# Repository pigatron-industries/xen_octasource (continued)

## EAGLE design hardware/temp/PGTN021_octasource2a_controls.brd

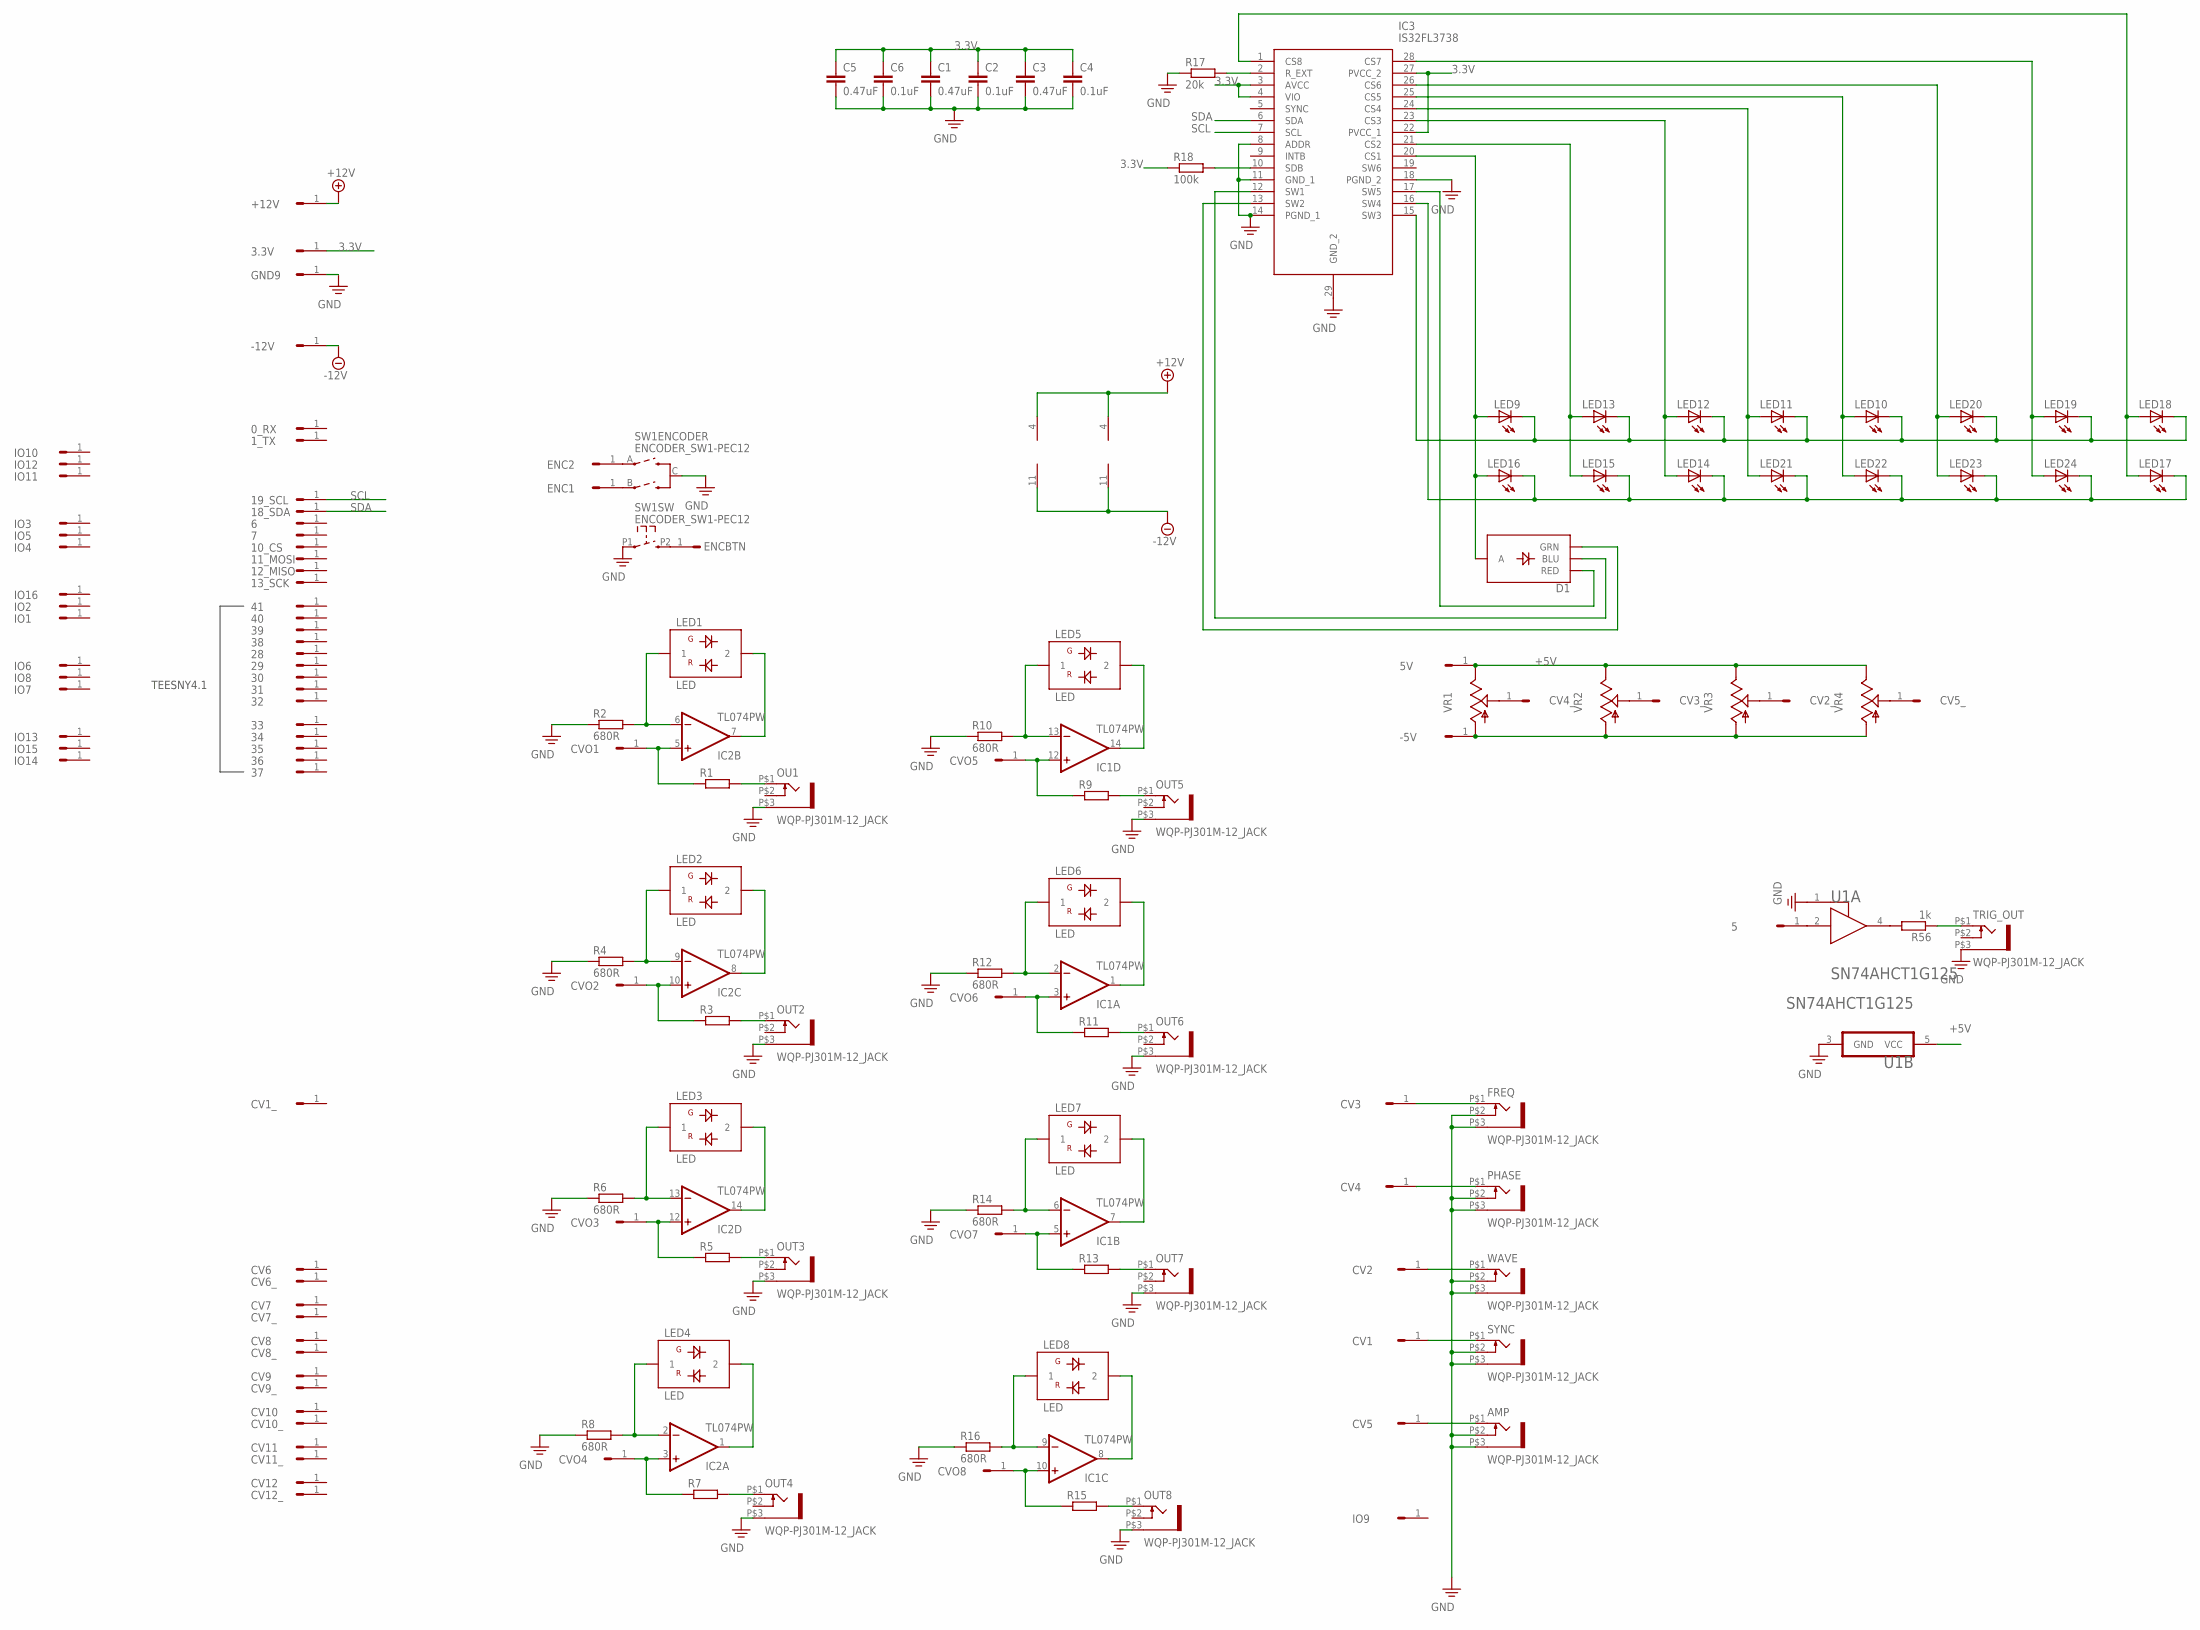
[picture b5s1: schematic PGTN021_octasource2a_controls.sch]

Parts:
0_RX, 1_TX, 3.3V, 5, 5V, 6, 7, 10_CS, 11_MOSI, 12_MISO, 13_SCK, 18_SDA, 19_SCL, 28, 29, 30, 31, 32, 33, 34, 35, 36, 37, 38, 39, 40, 41: HEADER/MALE/01
+12V: HEADER/MALE/01
-5V, -12V: HEADER/MALE/01
AMP: WQP-PJ301M-12_JACK
C1, C3, C5: 0.47uF; C0603
C2, C4, C6: 0.1uF; C0603
CV1, CV1_, CV2, CV2_, CV3, CV3_, CV4, CV4_, CV5, CV5_, CV6, CV6_, CV7, CV7_, CV8, CV8_, CV9, CV9_, CV10, CV10_, CV11, CV11_, CV12, CV12_: HEADER/MALE/01
CVO1, CVO2, CVO3, CVO4, CVO5, CVO6, CVO7, CVO8: HEADER/MALE/01
D1: LED-RGB-CADIALIGHT1210; CHIPLED_1210
ENC1, ENC2: HEADER/MALE/01
ENCBTN: HEADER/MALE/01
FREQ: WQP-PJ301M-12_JACK
GND9: HEADER/MALE/01
IC1, IC2: TL074PW; TSSOP14
IC3: IS32FL3738; TSSOP29
IO1, IO2, IO3, IO4, IO5, IO6, IO7, IO8, IO9, IO10, IO11, IO12, IO13, IO14, IO15, IO16: HEADER/MALE/01
LED1, LED2, LED3, LED4, LED5, LED6, LED7, LED8: LED; OG-LEDS_LED3MM
LED9, LED10, LED11, LED12, LED13, LED14, LED15, LED16, LED17, LED18, LED19, LED20, LED21, LED22, LED23, LED24: LEDCHIPLED_0805; CHIPLED_0805
OU1: WQP-PJ301M-12_JACK
OUT2, OUT3, OUT4, OUT5, OUT6, OUT7, OUT8: WQP-PJ301M-12_JACK
PHASE: WQP-PJ301M-12_JACK
R1, R3, R5, R7, R9, R11, R13, R15: RESISTOR; R0603
R2, R4, R6, R8, R10, R12, R14, R16: 680R; R0603
R17: 20k; R0603
R18: 100k; R0603
R56: 1k; R0603
SW1: ENCODER_SW1-PEC12; PEC12_INCREMENTAL_ENCODER
SYNC: WQP-PJ301M-12_JACK
TRIG_OUT: WQP-PJ301M-12_JACK
U1: 74AHCT1G125"; 74AHCT1G125
VR1, VR2, VR3, VR4: 9MM_SNAP-IN_POT_; 9MM_SNAP-IN_POT
WAVE: WQP-PJ301M-12_JACK

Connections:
3.3V: 3.3V.1, C1.1, C2.1, C3.1, C4.1, C5.1, C6.1, IC3.3 (AVCC), IC3.4 (VIO), IC3.22 (PVCC_1), IC3.27 (PVCC_2), R18.1
+5V: 5V.1, U1.5 (VCC), VR1.3 (E), VR2.3 (E), VR3.3 (E), VR4.3 (E)
+12V: +12V.1, IC1.4 (V+), IC2.4 (V+)
-12V: -12V.1, IC1.11 (V-), IC2.11 (V-)
unnamed: IC2.6 (-IN), LED1.1, R2.2
unnamed: IC2.7 (OUT), LED1.2
unnamed: CVO1.1, IC2.5 (+IN), R1.1
unnamed: OU1.P$1 (2), R1.2
unnamed: IC2.9 (-IN), LED2.1, R4.2
unnamed: IC2.8 (OUT), LED2.2
unnamed: CVO2.1, IC2.10 (+IN), R3.1
unnamed: OUT2.P$1 (2), R3.2
unnamed: IC2.13 (-IN), LED3.1, R6.2
unnamed: IC2.14 (OUT), LED3.2
unnamed: CVO3.1, IC2.12 (+IN), R5.1
unnamed: OUT3.P$1 (2), R5.2
unnamed: IC2.2 (-IN), LED4.1, R8.2
unnamed: IC2.1 (OUT), LED4.2
unnamed: CVO4.1, IC2.3 (+IN), R7.1
unnamed: OUT4.P$1 (2), R7.2
unnamed: IC1.13 (-IN), LED5.1, R10.2
unnamed: IC1.14 (OUT), LED5.2
unnamed: CVO5.1, IC1.12 (+IN), R9.1
unnamed: OUT5.P$1 (2), R9.2
unnamed: IC1.2 (-IN), LED6.1, R12.2
unnamed: IC1.1 (OUT), LED6.2
unnamed: CVO6.1, IC1.3 (+IN), R11.1
unnamed: OUT6.P$1 (2), R11.2
unnamed: IC1.6 (-IN), LED7.1, R14.2
unnamed: IC1.7 (OUT), LED7.2
unnamed: CVO7.1, IC1.5 (+IN), R13.1
unnamed: OUT7.P$1 (2), R13.2
unnamed: IC1.9 (-IN), LED8.1, R16.2
unnamed: IC1.8 (OUT), LED8.2
unnamed: CVO8.1, IC1.10 (+IN), R15.1
unnamed: OUT8.P$1 (2), R15.2
unnamed: IC3.10 (SDB), R18.2
unnamed: R56.2, U1.4 (Y)
unnamed: 5.1, U1.2 (A)
unnamed: ENCBTN.1, SW1.P2 (2)
unnamed: ENC2.1, SW1.A
unnamed: ENC1.1, SW1.B
unnamed: CV1.1, SYNC.P$1 (2)
unnamed: -5V.1, VR1.1 (A), VR2.1 (A), VR3.1 (A), VR4.1 (A)
unnamed: CV2.1, WAVE.P$1 (2)
unnamed: CV3.1, FREQ.P$1 (2)
unnamed: CV4.1, PHASE.P$1 (2)
unnamed: AMP.P$1 (2), CV5.1
unnamed: CV2_.1, VR3.2 (S)
unnamed: CV3_.1, VR2.2 (S)
unnamed: CV4_.1, VR1.2 (S)
unnamed: CV5_.1, VR4.2 (S)
unnamed: R56.1, TRIG_OUT.P$1 (2)
unnamed: D1.4 (A), IC3.20 (CS1), LED9.A, LED16.A
unnamed: IC3.21 (CS2), LED13.A, LED15.A
unnamed: IC3.23 (CS3), LED12.A, LED14.A
unnamed: D1.2 (RED), IC3.17 (SW5)
unnamed: D1.1 (BLU), IC3.12 (SW1)
unnamed: D1.3 (GRN), IC3.13 (SW2)
unnamed: IC3.16 (SW4), LED14.C, LED15.C, LED16.C, LED17.C, LED21.C, LED22.C, LED23.C, LED24.C
unnamed: IC3.15 (SW3), LED9.C, LED10.C, LED11.C, LED12.C, LED13.C, LED18.C, LED19.C, LED20.C
unnamed: IC3.24 (CS4), LED11.A, LED21.A
unnamed: IC3.25 (CS5), LED10.A, LED22.A
unnamed: IC3.26 (CS6), LED20.A, LED23.A
unnamed: IC3.28 (CS7), LED19.A, LED24.A
unnamed: IC3.1 (CS8), LED17.A, LED18.A
unnamed: IC3.2 (R_EXT), R17.2
PE: AMP.P$2 (3), AMP.P$3 (1), C1.2, C2.2, C3.2, C4.2, C5.2, C6.2, FREQ.P$2 (3), FREQ.P$3 (1), GND9.1, IC3.8 (ADDR), IC3.11 (GND_1), IC3.14 (PGND_1), IC3.18 (PGND_2), IC3.29 (GND_2), OU1.P$3 (1), OUT2.P$3 (1), OUT3.P$3 (1), OUT4.P$3 (1), OUT5.P$3 (1), OUT6.P$3 (1), OUT7.P$3 (1), OUT8.P$3 (1), PHASE.P$2 (3), PHASE.P$3 (1), R2.1, R4.1, R6.1, R8.1, R10.1, R12.1, R14.1, R16.1, R17.1, SW1.C, SW1.P1 (1), SYNC.P$2 (3), SYNC.P$3 (1), TRIG_OUT.P$3 (1), U1.1 (!OE!), U1.3 (GND), WAVE.P$2 (3), WAVE.P$3 (1)
SCL: 19_SCL.1, IC3.7 (SCL)
SDA: 18_SDA.1, IC3.6 (SDA)

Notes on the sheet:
TEESNY4.1

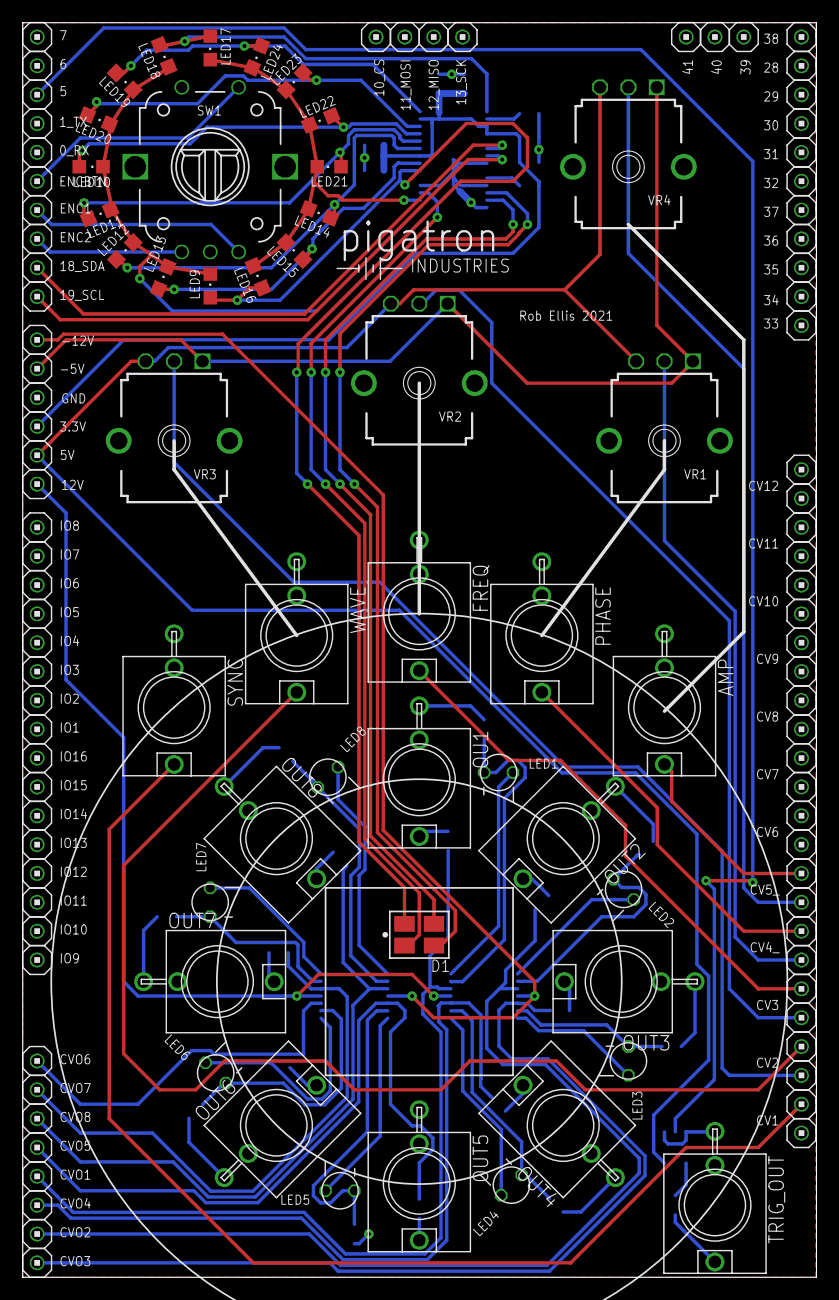
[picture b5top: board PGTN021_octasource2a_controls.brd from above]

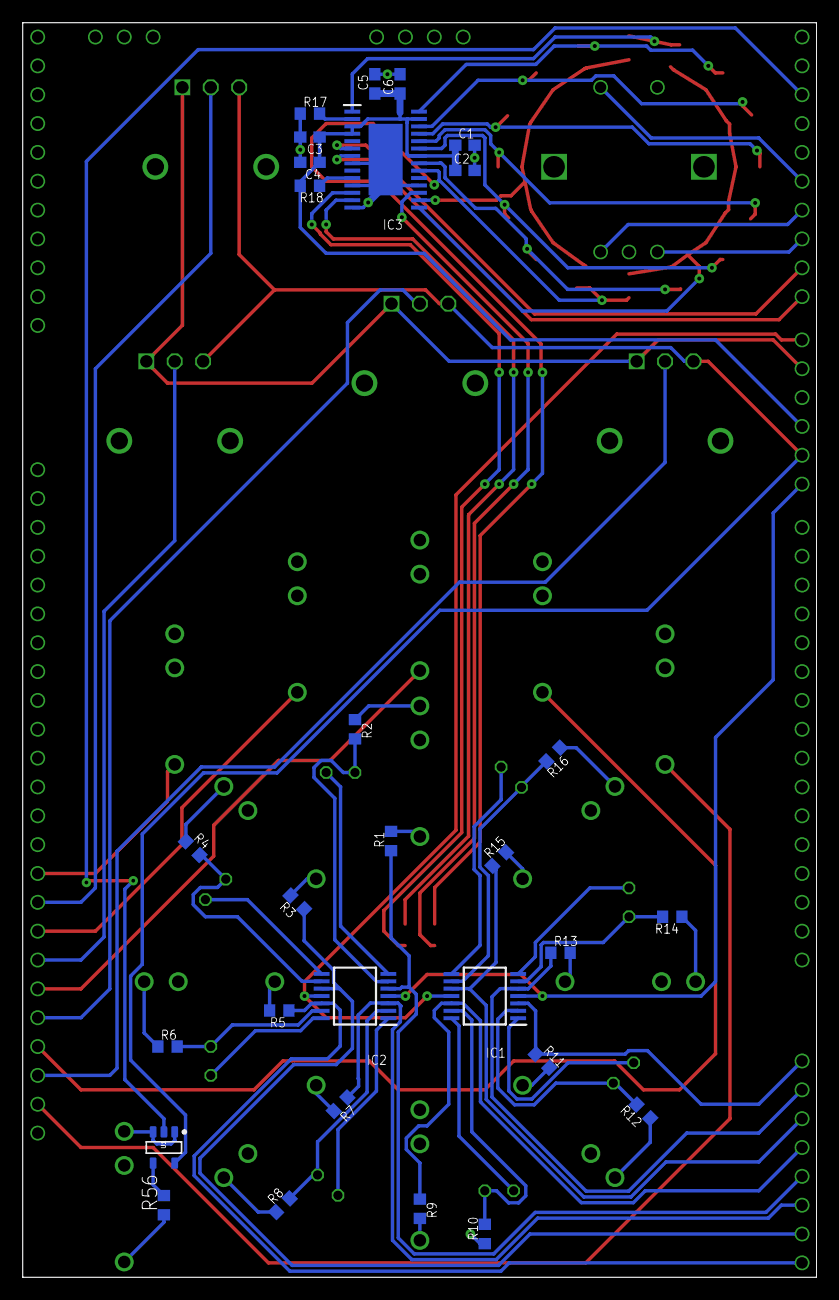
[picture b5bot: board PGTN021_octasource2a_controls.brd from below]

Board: 2 copper layers, 69.9 x 110.5 mm, 156 parts (29 on the bottom side), 70 nets.

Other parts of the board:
U$1: PIGATRON-LOGO

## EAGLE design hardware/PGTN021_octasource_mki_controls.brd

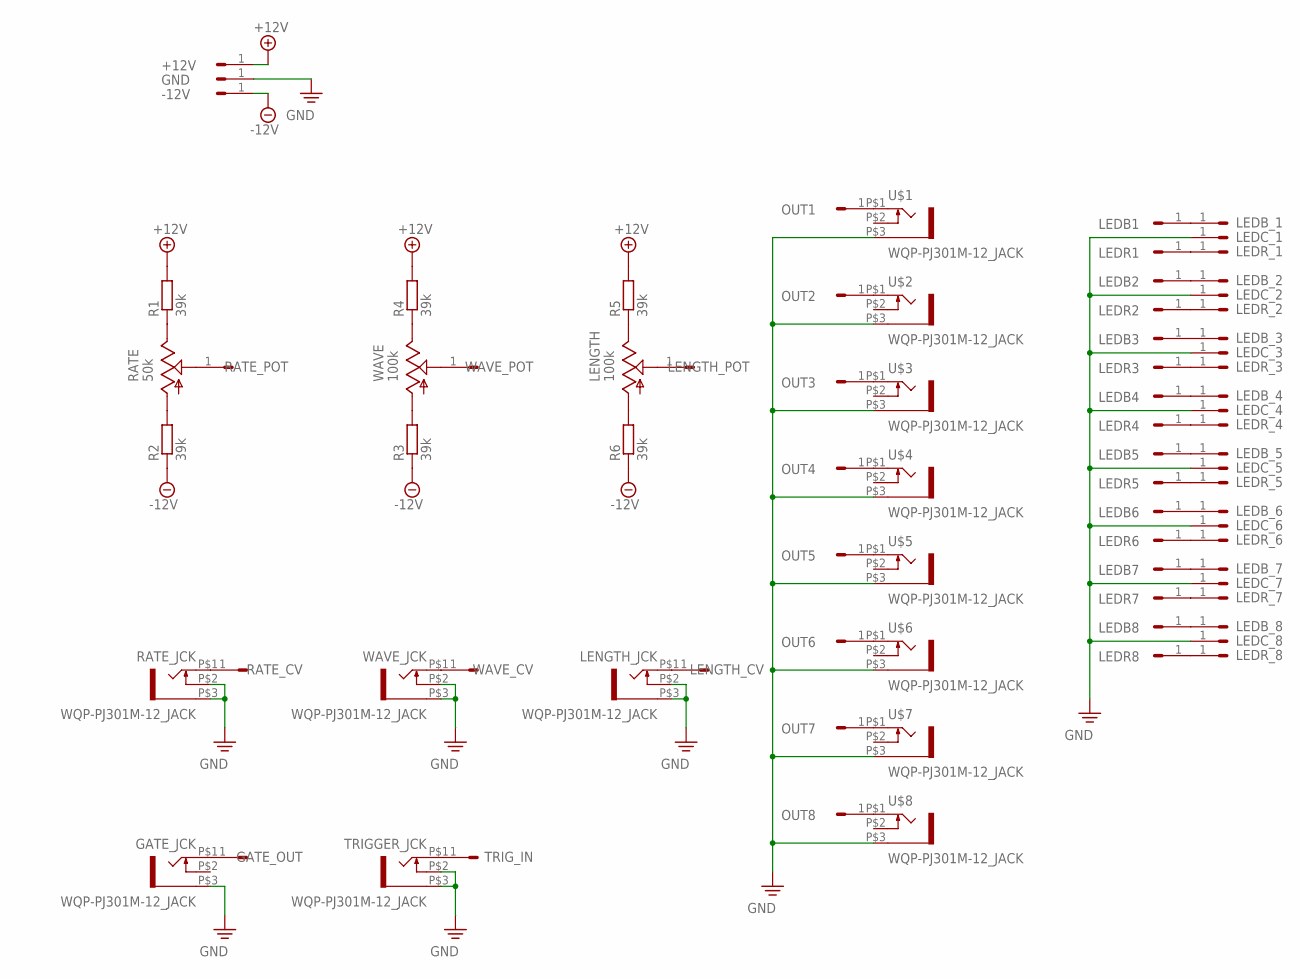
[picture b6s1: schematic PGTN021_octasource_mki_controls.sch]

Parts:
+12V: HEADER/MALE/01
-12V: HEADER/MALE/01
GATE_JCK: WQP-PJ301M-12_JACK
GATE_OUT: HEADER/MALE/01
GND: HEADER/MALE/01
LEDB1, LEDB2, LEDB3, LEDB4, LEDB5, LEDB6, LEDB7, LEDB8: HEADER/MALE/01
LEDB_1, LEDB_2, LEDB_3, LEDB_4, LEDB_5, LEDB_6, LEDB_7, LEDB_8: HEADER/MALE/01
LEDC_1, LEDC_2, LEDC_3, LEDC_4, LEDC_5, LEDC_6, LEDC_7, LEDC_8: HEADER/MALE/01
LEDR1, LEDR2, LEDR3, LEDR4, LEDR5, LEDR6, LEDR7, LEDR8: HEADER/MALE/01
LEDR_1, LEDR_2, LEDR_3, LEDR_4, LEDR_5, LEDR_6, LEDR_7, LEDR_8: HEADER/MALE/01
LENGTH: 100k; 9MM_SNAP-IN_POT
LENGTH_CV: HEADER/MALE/01
LENGTH_JCK: WQP-PJ301M-12_JACK
LENGTH_POT: HEADER/MALE/01
OUT1, OUT2, OUT3, OUT4, OUT5, OUT6, OUT7, OUT8: HEADER/MALE/01
R1, R2, R3, R4, R5, R6: 39k; RESISTOR/7.5
RATE: 50k; 9MM_SNAP-IN_POT
RATE_CV: HEADER/MALE/01
RATE_JCK: WQP-PJ301M-12_JACK
RATE_POT: HEADER/MALE/01
TRIGGER_JCK: WQP-PJ301M-12_JACK
TRIG_IN: HEADER/MALE/01
U$1, U$2, U$3, U$4, U$5, U$6, U$7, U$8: WQP-PJ301M-12_JACK
WAVE: 100k; 9MM_SNAP-IN_POT
WAVE_CV: HEADER/MALE/01
WAVE_JCK: WQP-PJ301M-12_JACK
WAVE_POT: HEADER/MALE/01

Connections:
+12V: +12V.1, R1.2, R4.2, R5.2
-12V: -12V.1, R2.1, R3.1, R6.1
unnamed: R2.2, RATE.1 (A)
unnamed: R1.1, RATE.3 (E)
unnamed: RATE_CV.1, RATE_JCK.P$1 (2)
unnamed: RATE.2 (S), RATE_POT.1
unnamed: R3.2, WAVE.1 (A)
unnamed: R4.1, WAVE.3 (E)
unnamed: WAVE.2 (S), WAVE_POT.1
unnamed: LENGTH.3 (E), R5.1
unnamed: LENGTH.1 (A), R6.2
unnamed: LENGTH.2 (S), LENGTH_POT.1
unnamed: LENGTH_CV.1, LENGTH_JCK.P$1 (2)
unnamed: WAVE_CV.1, WAVE_JCK.P$1 (2)
unnamed: GATE_JCK.P$1 (2), GATE_OUT.1
unnamed: OUT1.1, U$1.P$1 (2)
unnamed: OUT2.1, U$2.P$1 (2)
unnamed: OUT3.1, U$3.P$1 (2)
unnamed: OUT4.1, U$4.P$1 (2)
unnamed: OUT5.1, U$5.P$1 (2)
unnamed: OUT6.1, U$6.P$1 (2)
unnamed: OUT7.1, U$7.P$1 (2)
unnamed: OUT8.1, U$8.P$1 (2)
unnamed: LEDB1.1, LEDB_1.1
unnamed: LEDB2.1, LEDB_2.1
unnamed: LEDB3.1, LEDB_3.1
unnamed: LEDB4.1, LEDB_4.1
unnamed: LEDB5.1, LEDB_5.1
unnamed: LEDB6.1, LEDB_6.1
unnamed: LEDB7.1, LEDB_7.1
unnamed: LEDB8.1, LEDB_8.1
unnamed: LEDR1.1, LEDR_1.1
unnamed: LEDR2.1, LEDR_2.1
unnamed: LEDR3.1, LEDR_3.1
unnamed: LEDR4.1, LEDR_4.1
unnamed: LEDR5.1, LEDR_5.1
unnamed: LEDR6.1, LEDR_6.1
unnamed: LEDR7.1, LEDR_7.1
unnamed: LEDR8.1, LEDR_8.1
unnamed: TRIGGER_JCK.P$1 (2), TRIG_IN.1
PE: GATE_JCK.P$3 (1), GND.1, LEDC_1.1, LEDC_2.1, LEDC_3.1, LEDC_4.1, LEDC_5.1, LEDC_6.1, LEDC_7.1, LEDC_8.1, LENGTH_JCK.P$2 (3), LENGTH_JCK.P$3 (1), RATE_JCK.P$2 (3), RATE_JCK.P$3 (1), TRIGGER_JCK.P$2 (3), TRIGGER_JCK.P$3 (1), U$1.P$3 (1), U$2.P$3 (1), U$3.P$3 (1), U$4.P$3 (1), U$5.P$3 (1), U$6.P$3 (1), U$7.P$3 (1), U$8.P$3 (1), WAVE_JCK.P$2 (3), WAVE_JCK.P$3 (1)

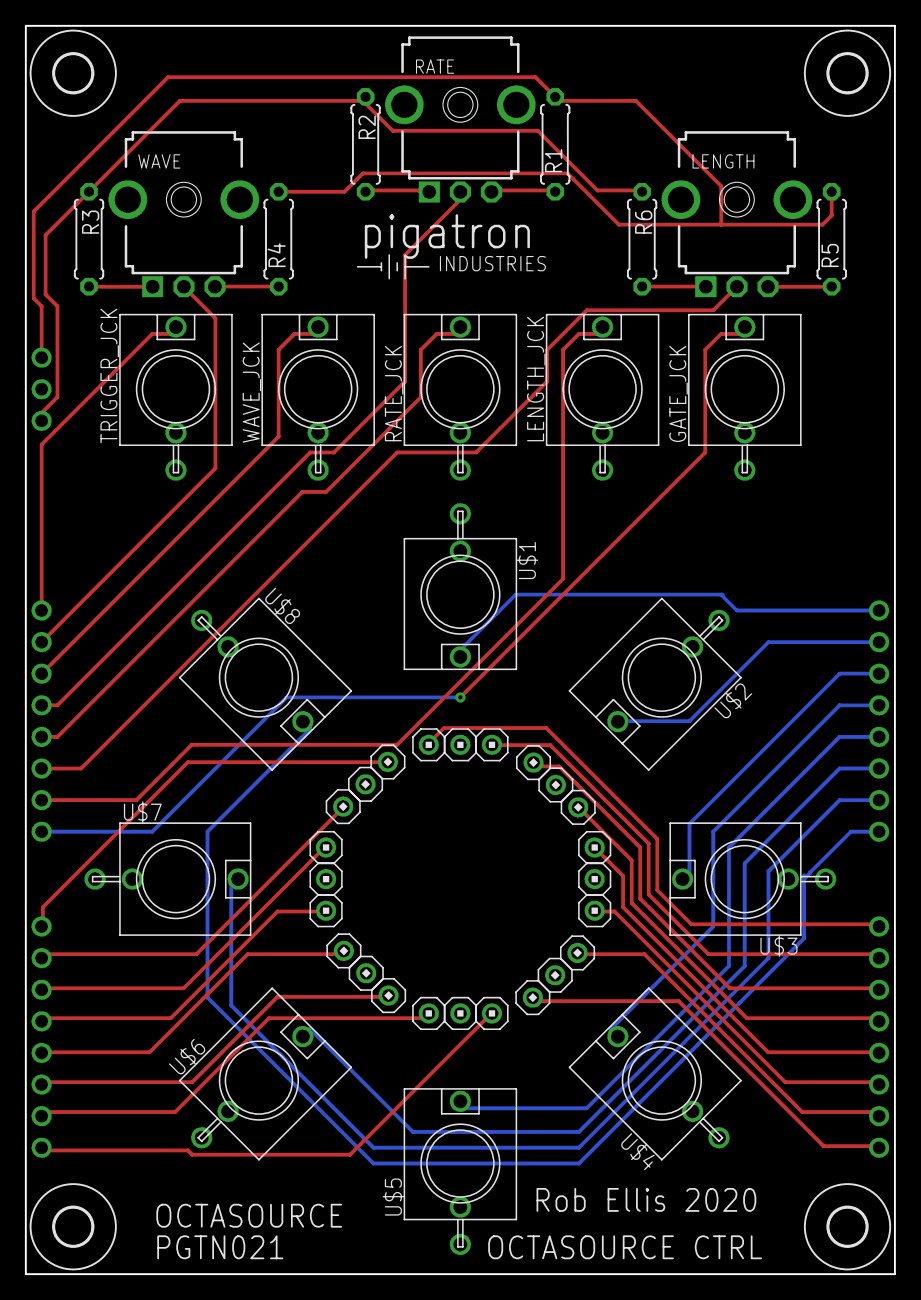
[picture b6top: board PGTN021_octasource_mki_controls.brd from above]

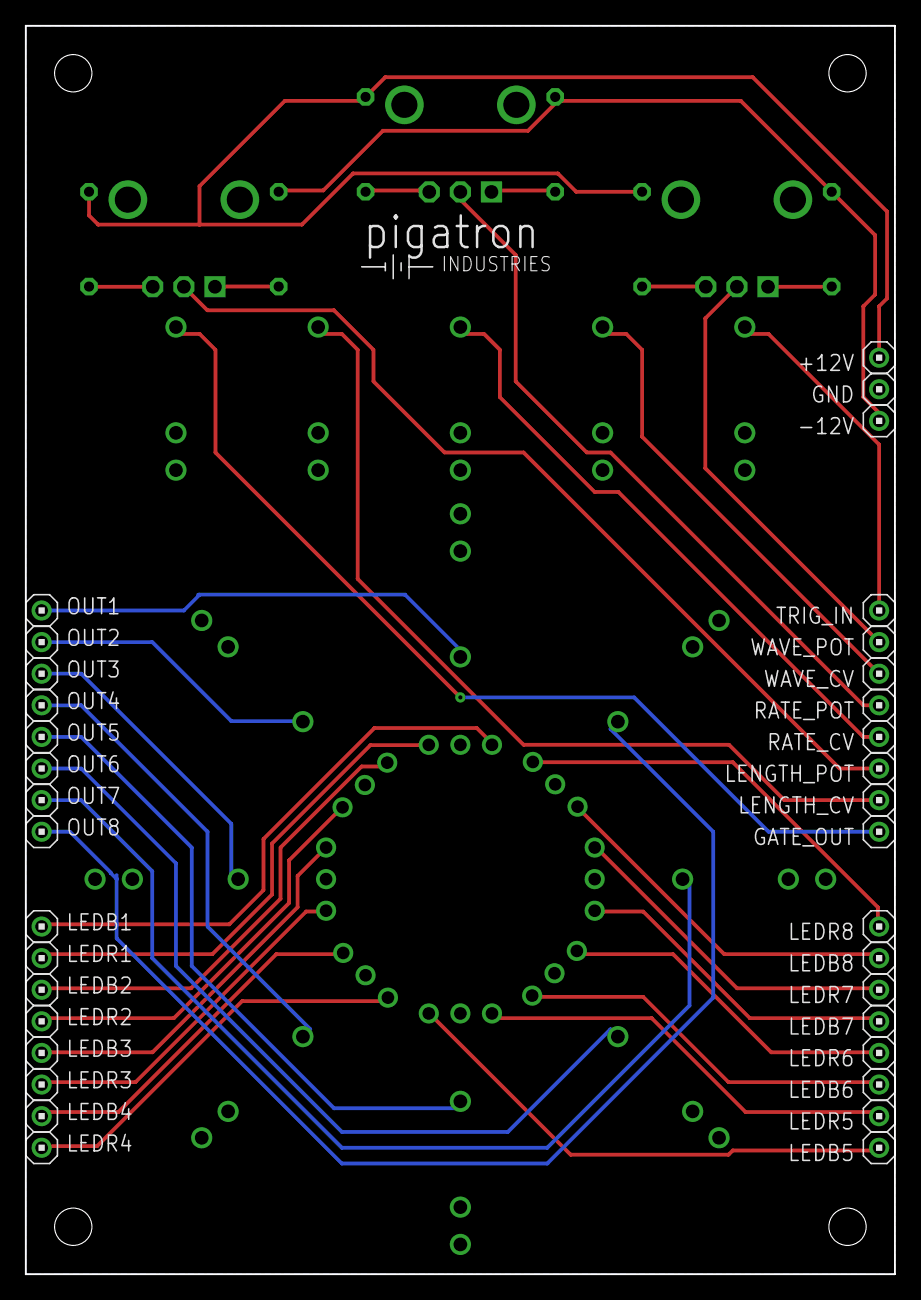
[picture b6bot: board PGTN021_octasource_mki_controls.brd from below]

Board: 2 copper layers, 69.8 x 100.3 mm, 87 parts (36 on the bottom side), 41 nets.

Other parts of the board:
U$9, U$10, U$11, U$12: STANDOFF/3.0
U$13, U$14: PIGATRON-LOGO

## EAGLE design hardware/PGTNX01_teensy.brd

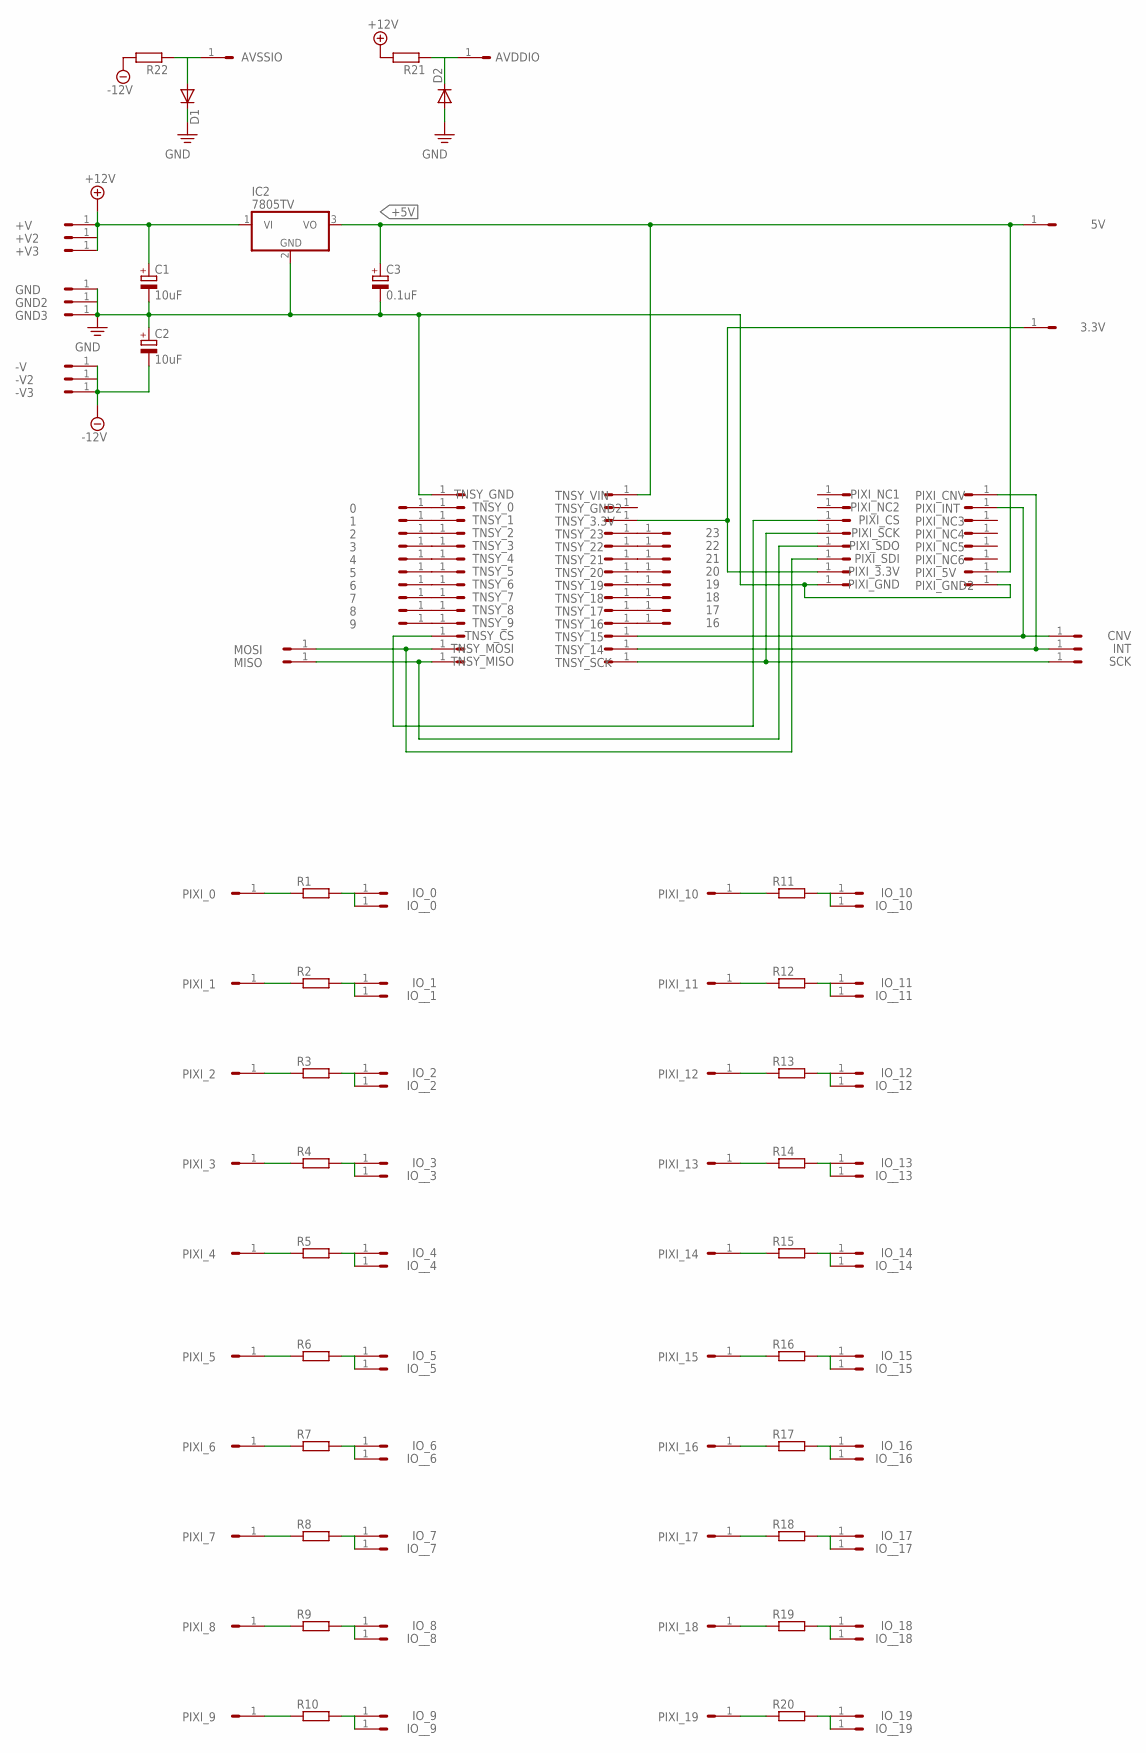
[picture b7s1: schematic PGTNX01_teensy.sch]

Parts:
0, 1, 2, 3, 3.3V, 4, 5, 5V, 6, 7, 8, 9, 16, 17, 18, 19, 20, 21, 22, 23: HEADER/MALE/01
+V, +V2, +V3: HEADER/MALE/01
-V, -V2, -V3: HEADER/MALE/01
AVDDIO: HEADER/MALE/01
AVSSIO: HEADER/MALE/01
C1, C2: 10uF; E2,5-6
C3: 0.1uF; E2,5-6
CNV: HEADER/MALE/01
D1, D2: 1N4148DO35-7; DO35-7
GND, GND2, GND3: HEADER/MALE/01
IC2: 7805TV; TO220V
INT: HEADER/MALE/01
IO_0, IO_1, IO_2, IO_3, IO_4, IO_5, IO_6, IO_7, IO_8, IO_9, IO_10, IO_11, IO_12, IO_13, IO_14, IO_15, IO_16, IO_17, IO_18, IO_19: HEADER/MALE/01
IO__0, IO__1, IO__2, IO__3, IO__4, IO__5, IO__6, IO__7, IO__8, IO__9, IO__10, IO__11, IO__12, IO__13, IO__14, IO__15, IO__16, IO__17, IO__18, IO__19: HEADER/MALE/01
MISO: HEADER/MALE/01
MOSI: HEADER/MALE/01
PIXI_0, PIXI_1, PIXI_2, PIXI_3, PIXI_3.3V, PIXI_4, PIXI_5, PIXI_5V, PIXI_6, PIXI_7, PIXI_8, PIXI_9, PIXI_10, PIXI_11, PIXI_12, PIXI_13, PIXI_14, PIXI_15, PIXI_16, PIXI_17, PIXI_18, PIXI_19: HEADER/MALE/01
PIXI_CNV: HEADER/MALE/01
PIXI_CS: HEADER/MALE/01
PIXI_GND, PIXI_GND2: HEADER/MALE/01
PIXI_INT: HEADER/MALE/01
PIXI_NC1, PIXI_NC2, PIXI_NC3, PIXI_NC4, PIXI_NC5, PIXI_NC6: HEADER/MALE/01
PIXI_SCK: HEADER/MALE/01
PIXI_SDI: HEADER/MALE/01
PIXI_SDO: HEADER/MALE/01
R1, R2, R3, R4, R5, R6, R7, R8, R9, R10, R11, R12, R13, R14, R15, R16, R17, R18, R19, R20, R21, R22: RESISTORRESISTOR/UPRIGHT/7.5; RESISTOR/7.5
SCK: HEADER/MALE/01
TNSY_0, TNSY_1, TNSY_2, TNSY_3, TNSY_3.3V, TNSY_4, TNSY_5, TNSY_6, TNSY_7, TNSY_8, TNSY_9, TNSY_14, TNSY_15, TNSY_16, TNSY_17, TNSY_18, TNSY_19, TNSY_20, TNSY_21, TNSY_22, TNSY_23: HEADER/MALE/01
TNSY_CS: HEADER/MALE/01
TNSY_GND, TNSY_GND2: HEADER/MALE/01
TNSY_MISO: HEADER/MALE/01
TNSY_MOSI: HEADER/MALE/01
TNSY_SCK: HEADER/MALE/01
TNSY_VIN: HEADER/MALE/01

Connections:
+5V: 5V.1, C3.+, IC2.3 (VO), PIXI_5V.1, TNSY_VIN.1
+12V: +V.1, +V2.1, +V3.1, C1.+, IC2.1 (VI), R21.2
-12V: -V.1, -V2.1, -V3.1, C2.-, R22.2
GND: C1.-, C2.+, C3.-, D1.C, D2.A, GND.1, GND2.1, GND3.1, IC2.2 (GND), PIXI_GND.1, PIXI_GND2.1, TNSY_GND.1
unnamed: PIXI_0.1, R1.1
unnamed: 17.1, TNSY_17.1
unnamed: PIXI_1.1, R2.1
unnamed: 16.1, TNSY_16.1
unnamed: MOSI.1, PIXI_SDI.1, TNSY_MOSI.1
unnamed: MISO.1, PIXI_SDO.1, TNSY_MISO.1
unnamed: PIXI_SCK.1, SCK.1, TNSY_SCK.1
unnamed: PIXI_CS.1, TNSY_CS.1
unnamed: INT.1, PIXI_CNV.1, TNSY_14.1
unnamed: CNV.1, PIXI_INT.1, TNSY_15.1
unnamed: 18.1, TNSY_18.1
unnamed: 19.1, TNSY_19.1
unnamed: 20.1, TNSY_20.1
unnamed: 21.1, TNSY_21.1
unnamed: 22.1, TNSY_22.1
unnamed: 23.1, TNSY_23.1
unnamed: 0.1, TNSY_0.1
unnamed: 1.1, TNSY_1.1
unnamed: 2.1, TNSY_2.1
unnamed: 3.1, TNSY_3.1
unnamed: 4.1, TNSY_4.1
unnamed: 5.1, TNSY_5.1
unnamed: 6.1, TNSY_6.1
unnamed: 7.1, TNSY_7.1
unnamed: 8.1, TNSY_8.1
unnamed: 9.1, TNSY_9.1
unnamed: IO_1.1, IO__1.1, R2.2
unnamed: 3.3V.1, PIXI_3.3V.1, TNSY_3.3V.1
unnamed: IO_0.1, IO__0.1, R1.2
unnamed: PIXI_2.1, R3.1
unnamed: IO_2.1, IO__2.1, R3.2
unnamed: PIXI_3.1, R4.1
unnamed: IO_3.1, IO__3.1, R4.2
unnamed: PIXI_4.1, R5.1
unnamed: IO_4.1, IO__4.1, R5.2
unnamed: PIXI_5.1, R6.1
unnamed: IO_5.1, IO__5.1, R6.2
unnamed: PIXI_6.1, R7.1
unnamed: IO_6.1, IO__6.1, R7.2
unnamed: PIXI_7.1, R8.1
unnamed: IO_7.1, IO__7.1, R8.2
unnamed: PIXI_8.1, R9.1
unnamed: IO_8.1, IO__8.1, R9.2
unnamed: PIXI_9.1, R10.1
unnamed: IO_9.1, IO__9.1, R10.2
unnamed: PIXI_10.1, R11.1
unnamed: IO_10.1, IO__10.1, R11.2
unnamed: PIXI_11.1, R12.1
unnamed: IO_11.1, IO__11.1, R12.2
unnamed: PIXI_12.1, R13.1
unnamed: IO_12.1, IO__12.1, R13.2
unnamed: PIXI_13.1, R14.1
unnamed: IO_13.1, IO__13.1, R14.2
unnamed: PIXI_14.1, R15.1
unnamed: IO_14.1, IO__14.1, R15.2
unnamed: PIXI_15.1, R16.1
unnamed: IO_15.1, IO__15.1, R16.2
unnamed: PIXI_16.1, R17.1
unnamed: IO_16.1, IO__16.1, R17.2
unnamed: PIXI_17.1, R18.1
unnamed: IO_17.1, IO__17.1, R18.2
unnamed: PIXI_18.1, R19.1
unnamed: IO_18.1, IO__18.1, R19.2
unnamed: PIXI_19.1, R20.1
unnamed: IO_19.1, IO__19.1, R20.2
unnamed: AVDDIO.1, D2.C, R21.1
unnamed: AVSSIO.1, D1.A, R22.1

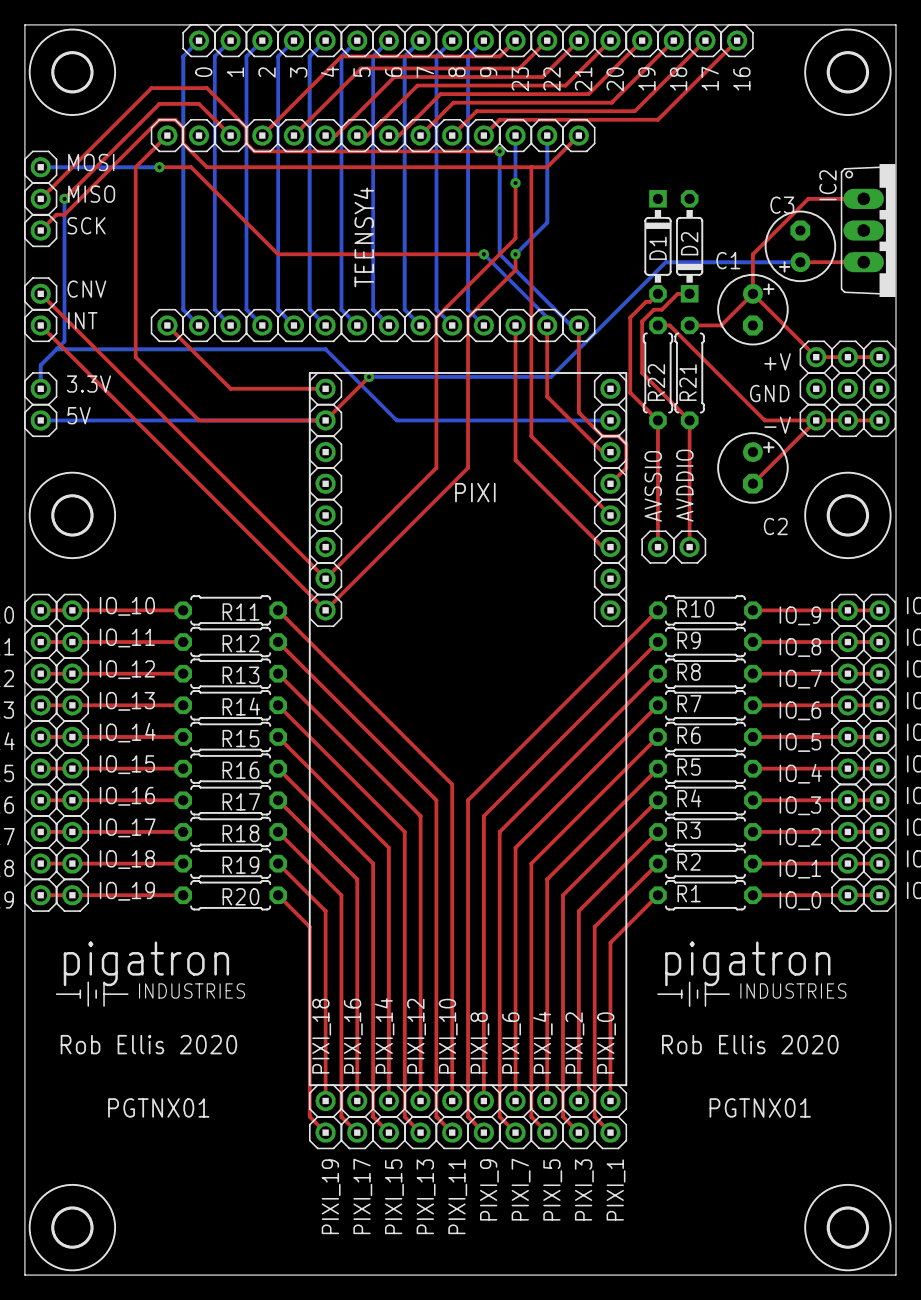
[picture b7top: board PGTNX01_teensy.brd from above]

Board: 2 copper layers, 69.9 x 100.3 mm, 176 parts (0 on the bottom side), 71 nets.

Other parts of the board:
U$1, U$2, U$3, U$4, U$6, U$7: STANDOFF/3.0
U$5, U$8: PIGATRON-LOGO
